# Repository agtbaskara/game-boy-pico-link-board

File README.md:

# USB TO GAMEBOY LINK CABLE ADAPTER

> **This design has been superseded by [GB-Link-USB-DIY](https://github.com/GB-Link/GB-Link-USB-DIY). Please use that project instead.**

An Open-Source USB to Gameboy Link Cable Adapter for Raspberry Pi Pico. Designed with components that are easy to source and solder.

Based on stacksmashing Gameboy Link adapter: https://www.youtube.com/watch?v=KtHu693wE9o

# Schematic

# Required Components

| Reference | Part Number | Description |
|-|-|-|
| U1 | [Raspberry Pi Pico](https://www.raspberrypi.com/products/raspberry-pi-pico/) | Clones are compatible |
| U2 | [BOB-12009](https://www.sparkfun.com/products/12009) | Sparkfun Bi-Directional Logic Level Converter, clones are compatible |
| SW1 | [SS12D00-G3](https://www.amazon.com/Tnuocke-Vertical-Position-Switches-SS12D00-G3/dp/B099MRCDG8) | 3 Pin SPDT Switch with 1" (2.54mm) Pitch |

If you want to use pin jumper instead of switch you can use:

| Reference | Part Number | Description |
|-|-|-|
| SW1 | [Pin Header](https://www.amazon.com/dp/B07PKKY8BX) | 1x3 2.54mm Male Pin Header |
| - | [Pin Jumper](https://www.amazon.com/dp/B077957RN7) | 2.54mm Pin Jumper, harvest from old motherboard or hardrive |

**Attached links are for reference only, you can use any equivalent parts.**

**List of tested components** [Tested Components List](COMPONENTS.md)

# How to Order Board

To order a board, use the `gerbers.zip` from the release page or generate one yourself. You can order from your favourite PCB manufacturer ([JLCPCB](https://jlcpcb.com/), [PCBWay](https://www.pcbway.com/), etc.).

**Use 1.2mm PCB thickness.**

You can choose any colour for the Solder Mask and Silkscreen. For the Surface Finish, ENIG is recommended.

# How to Assemble Board

1. Trim the Link Cable connectors width on the board to the appropriate size using a file tool or sandpaper
2. Solder pin header to Raspberry Pi Pico and Level Shifter module. Use a breadboard for easier soldering
3. Solder Raspberry Pi Pico and Level Shifter module to the board
4. Cut the excessive pin using a nipper tool
5. Solder the 1x3 Pin Header to the board, and place the Pin Jumper
6. Flash firmware to your Raspberry Pi Pico (see [Compatibility](#Compatibility))

# How to Use Board

Connect the board to your PC, and connect the board to your Gameboy using a Link Cable.

For Gameboy/Gameboy Color game, place the pin jumper on the DMG/GBC side. For Gameboy Advance game, place the pin jumper on the GBA side.

**Be aware Gameboy/Gameboy Color mode uses 5V logic, while Gameboy Advance mode uses 3.3V logic. Make sure your pin jumper is placed on the correct side to avoid any damage.**

# Compatibility

This board is compatible with the following firmware:
- https://github.com/GB-Link/GBLink-Firmware (Recommended Firmware)
- https://github.com/Lorenzooone/gb-link-firmware-reconfigurable
- https://github.com/stacksmashing/gb-link-firmware
- https://github.com/stacksmashing/gb-link-printer
- https://github.com/Lorenzooone/PokemonGB_Online_Trades
- https://github.com/dj505/GBPrinterEmu
- https://github.com/Squaresweets/GBPrinter-discord-bot
- https://github.com/KuestenKeks/pc-to-gb-printer

With some modification, it should be compatible with other firmware as well, such as:
- https://github.com/untoxa/pico-gb-printer

# References

- Raspberry Pi Pico Footprint: https://github.com/ncarandini/KiCad-RP-Pico
- Logic Level Converter (BOB-12009) Footprint: https://www.snapeda.com/parts/BOB-12009/SparkFun%20Electronics/view-part/
- Gameboy Link Connector Footprint: https://github.com/Palmr/gb-link-cable
- 1.2mm PCB Thickness, based on: https://hackaday.io/project/12932-game-link-online/log/43999-received-the-breakout-boards

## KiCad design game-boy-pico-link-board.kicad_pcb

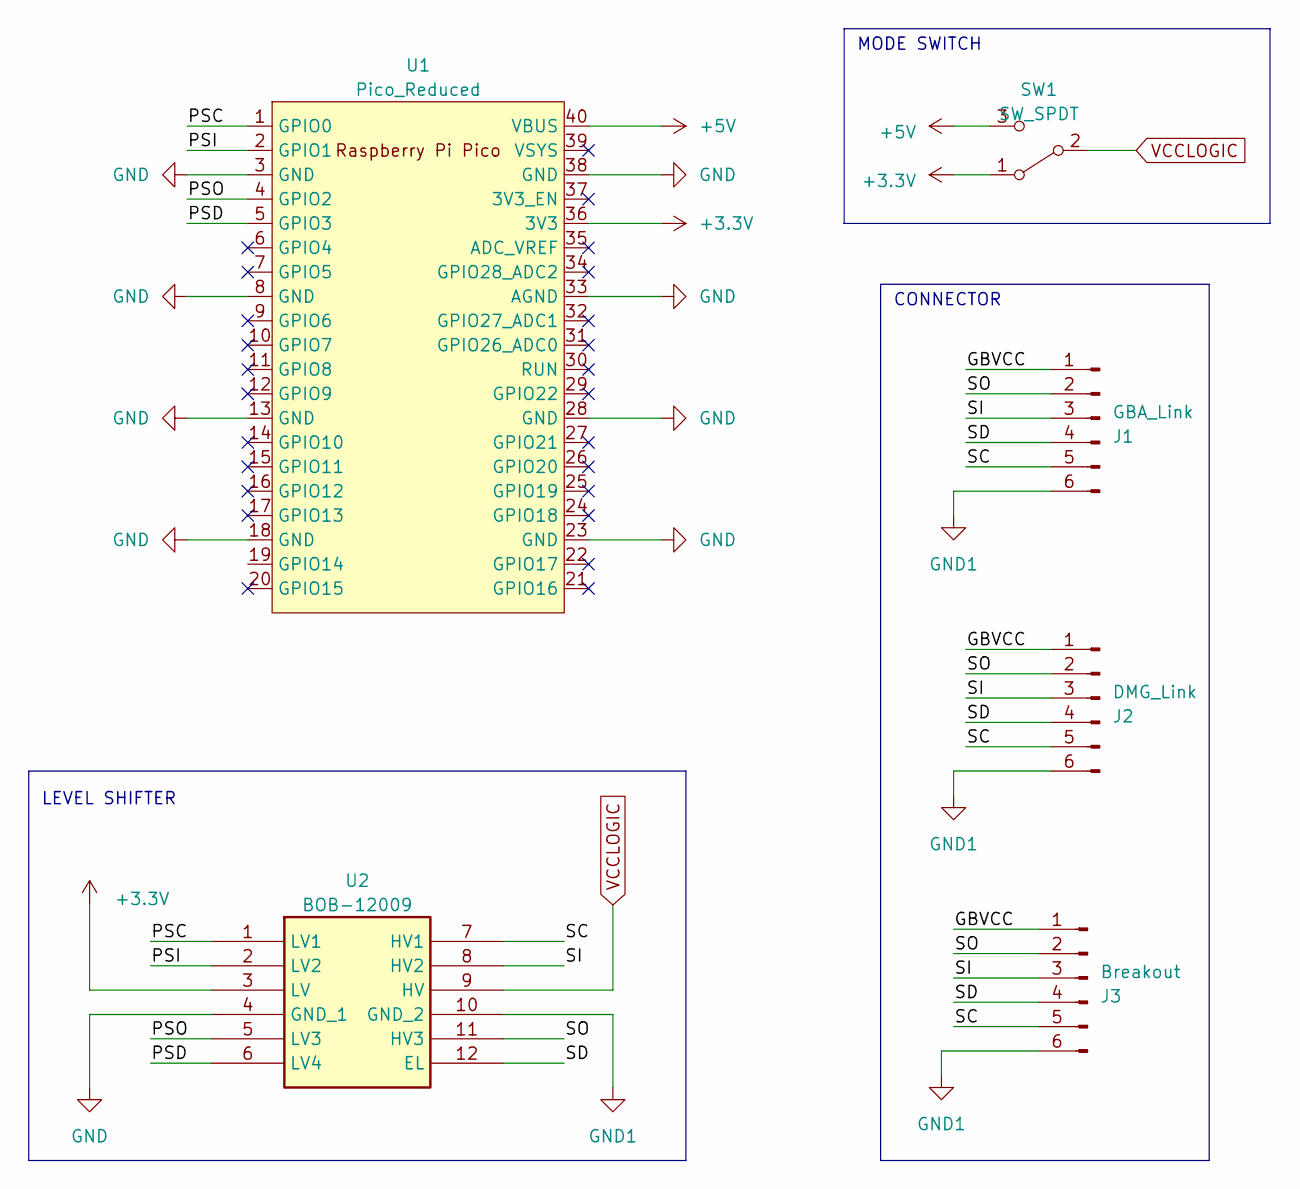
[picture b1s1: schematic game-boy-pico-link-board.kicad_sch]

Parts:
J1: GBA_Link; gb-link-socket
J2: DMG_Link; dmg-link-socket
J3: Breakout; PinHeader_1x06_P2.54mm_Vertical
SW1: SW_SPDT; PinHeader_1x03_P2.54mm_Vertical
U1: Pico_Reduced; RPi_Pico_SMD_TH_REDUCED
U2: BOB-12009

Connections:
+3.3V: SW1.1 (A), U1.36 (3V3), U2.3 (LV)
+5V: SW1.3 (C), U1.40 (VBUS)
/GBVCC: J1.1, J2.1, J3.1
/PSC: U1.1 (GPIO0), U2.1 (LV1)
/PSD: U1.5 (GPIO3), U2.6 (LV4)
/PSI: U1.2 (GPIO1), U2.2 (LV2)
/PSO: U1.4 (GPIO2), U2.5 (LV3)
/SC: J1.5, J2.5, J3.5, U2.7 (HV1)
/SD: J1.4, J2.4, J3.4, U2.12 (EL)
/SI: J1.3, J2.3, J3.3, U2.8 (HV2)
/SO: J1.2, J2.2, J3.2, U2.11 (HV3)
GND: U1.3 (GND), U1.8 (GND), U1.13 (GND), U1.18 (GND), U1.23 (GND), U1.28 (GND), U1.33 (AGND), U1.38 (GND), U2.4 (GND_1)
GND1: J1.6, J2.6, J3.6, U2.10 (GND_2)
VCCLOGIC: SW1.2 (B), U2.9 (HV)

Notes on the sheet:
LEVEL SHIFTER
MODE SWITCH
CONNECTOR

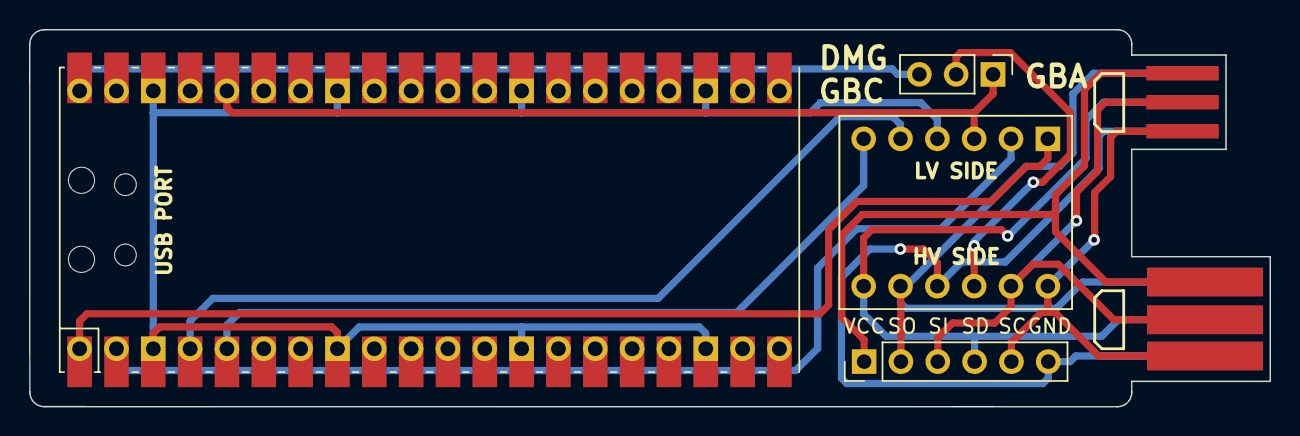
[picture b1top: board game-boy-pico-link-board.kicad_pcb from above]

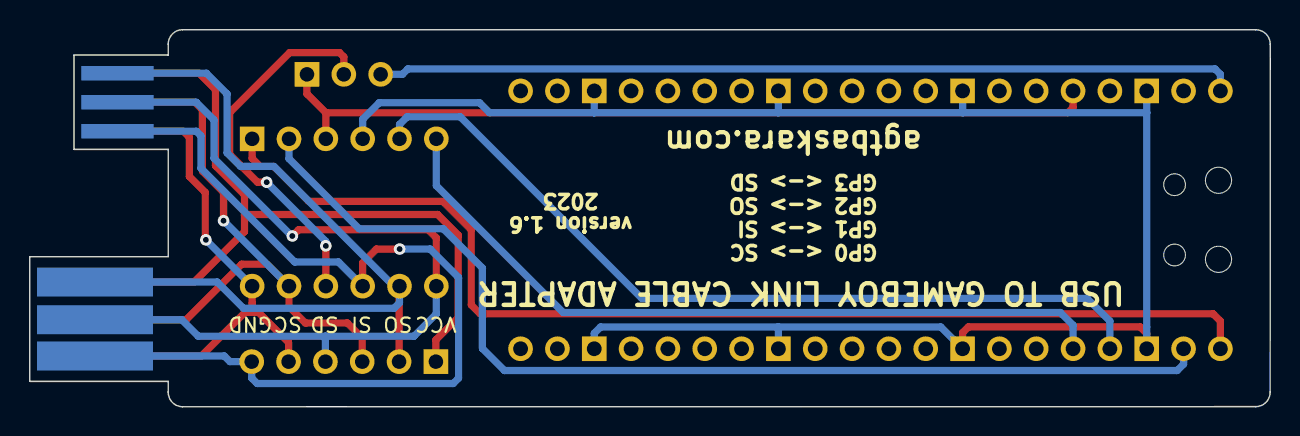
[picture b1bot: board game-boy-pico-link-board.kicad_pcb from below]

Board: 2 copper layers, 85.5 x 26.0 mm, 6 parts (2 on the bottom side), 14 nets.

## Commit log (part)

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2023-04-02 Add initial design
2023-05-27 Update Design and Add Routing
2023-05-27 Add gerbers file
2023-06-02 add LICENSE
2023-06-07 Update Design
    Shortened DMG socket
    Replace components layout
    Add more silkscreen text
2023-06-08 Update Connector Size
    Add extra 0.5mm padding on the connector width
2023-06-08 Update gerbers file
2023-06-09 Minor rerouting
    Update design to v1.6
2023-10-28 Update readme: replace pin jumper with switch
2023-12-02 Fix missing no-connection flag
2024-03-17 Add Tested Components List
